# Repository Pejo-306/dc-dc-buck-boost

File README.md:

# DC-DC Buck-Boost Converter - Diploma Project

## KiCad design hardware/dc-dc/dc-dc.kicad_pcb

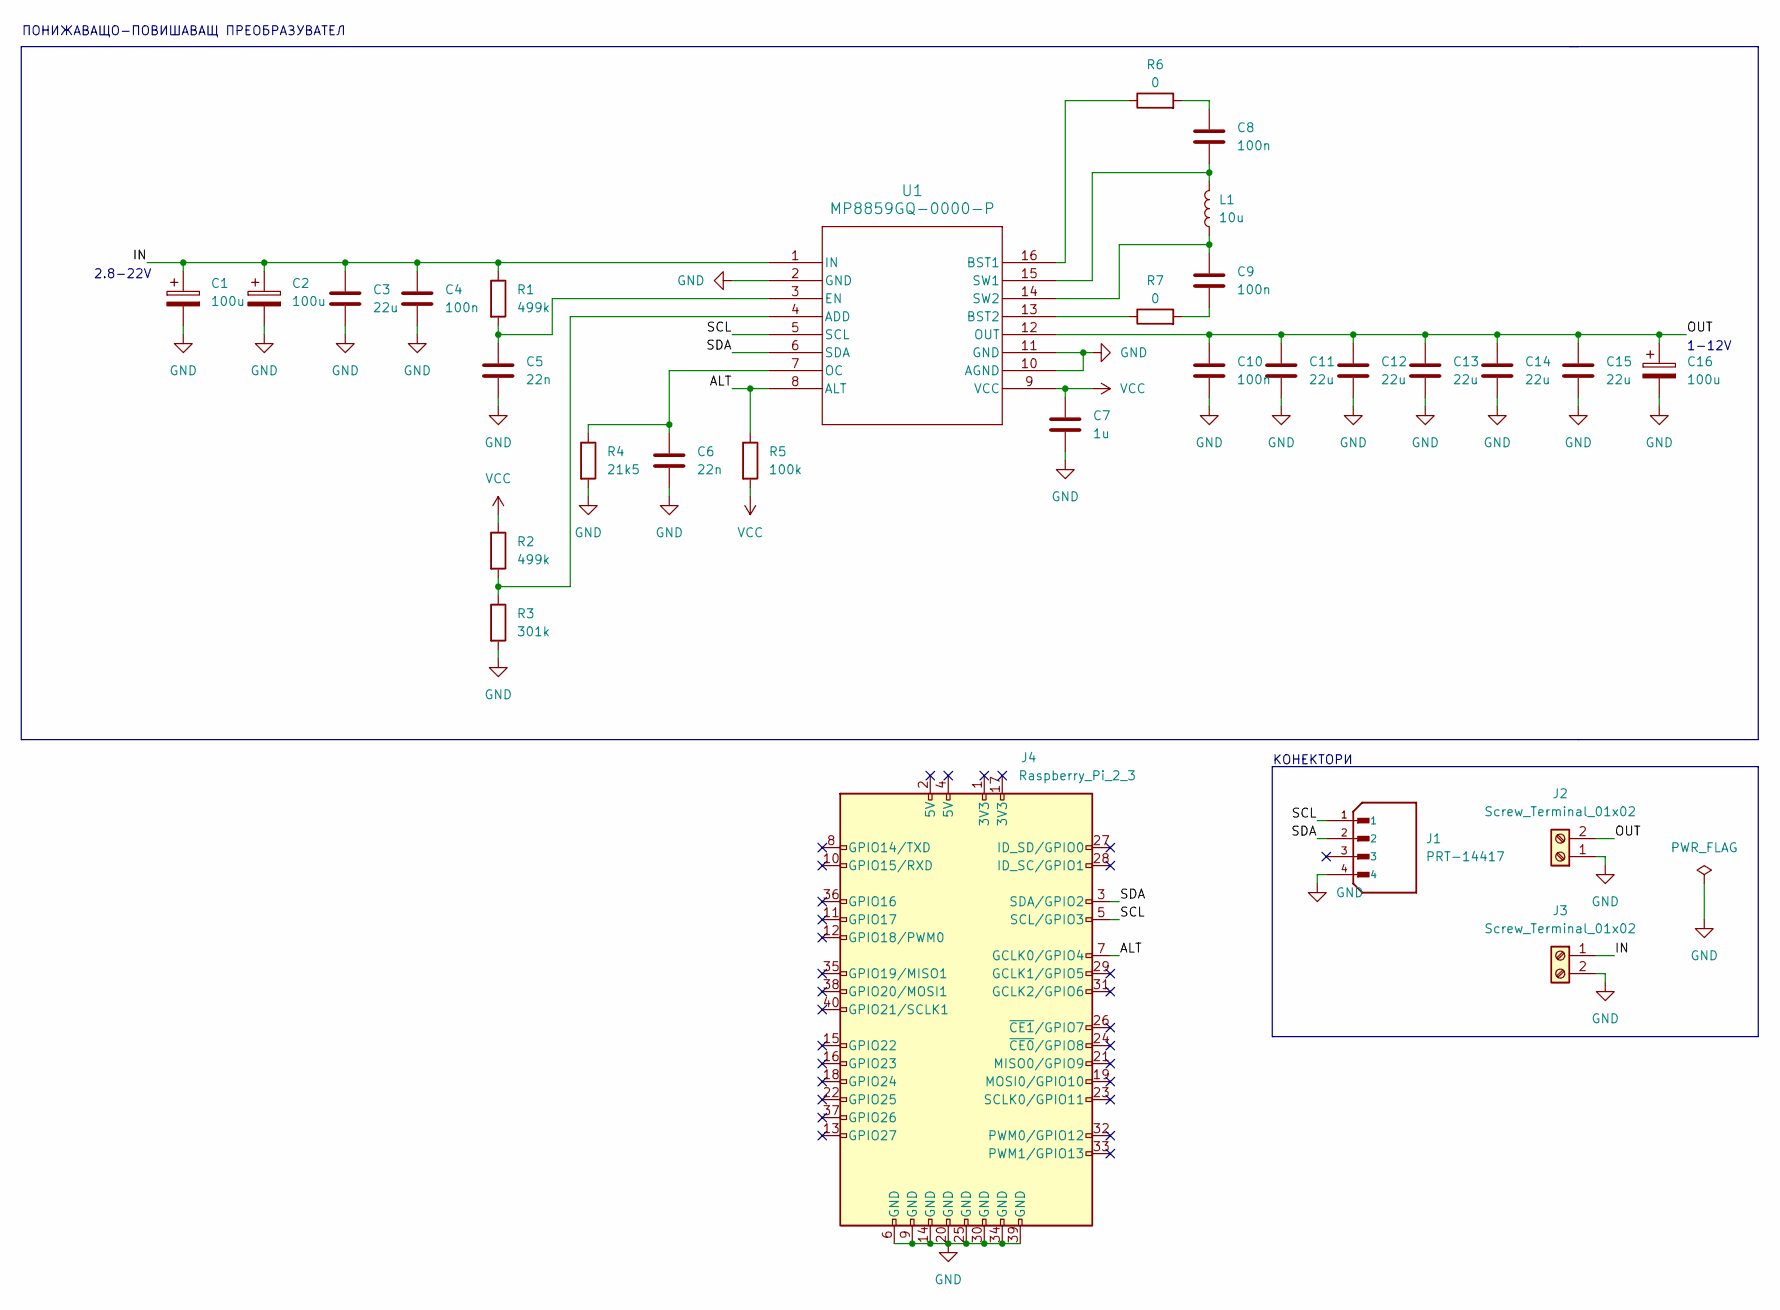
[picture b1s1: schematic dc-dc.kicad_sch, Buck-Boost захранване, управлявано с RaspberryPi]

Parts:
C1, C16: 100u; CP_Elec_6.3x7.7
C2: 100u; CP_EIA-7343-43_Kemet-X_Pad2.25x2.55mm_HandSolder
C3, C11, C12, C13, C14, C15: 22u; C_1206_3216Metric_Pad1.33x1.80mm_HandSolder
C4, C8, C9, C10: 100n; C_0402_1005Metric_Pad0.74x0.62mm_HandSolder
C5, C6: 22n; C_0402_1005Metric_Pad0.74x0.62mm_HandSolder
C7: 1u; C_0603_1608Metric_Pad1.08x0.95mm_HandSolder
J1: PRT-14417; SPARKFUN_PRT-14417; PARTREV NA
J2, J3: Screw_Terminal_01x02; TerminalBlock_Phoenix_PT-1,5-2-3.5-H_1x02_P3.50mm_Horizontal
J4: Raspberry_Pi_2_3
L1: 10u; IND_7050-WE-LHMI_WRE
R1, R2: 499k; R_0402_1005Metric_Pad0.72x0.64mm_HandSolder
R3: 301k; R_0402_1005Metric_Pad0.72x0.64mm_HandSolder
R4: 21k5; R_0402_1005Metric_Pad0.72x0.64mm_HandSolder
R5: 100k; R_0402_1005Metric_Pad0.72x0.64mm_HandSolder
R6, R7: 0; R_0402_1005Metric_Pad0.72x0.64mm_HandSolder
U1: MP8859GQ-0000-P; QFN-16_MP8859_00_MNP

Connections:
/ALT: J4.7 (GCLK0/GPIO4), R5.1, U1.8 (ALT)
/IN: C1.1, C2.1, C3.1, C4.1, J3.1, R1.1, U1.1 (IN)
/OUT: C10.1, C11.1, C12.1, C13.1, C14.1, C15.1, C16.1, J2.2, U1.12 (OUT)
/SCL: J1.1, J4.5 (SCL/GPIO3), U1.5 (SCL)
/SDA: J1.2, J4.3 (SDA/GPIO2), U1.6 (SDA)
GND: C1.2, C2.2, C3.2, C4.2, C5.2, C6.2, C7.2, C10.2, C11.2, C12.2, C13.2, C14.2, C15.2, C16.2, J1.4, J2.1, J3.2, J4.6 (GND), J4.9 (GND), J4.14 (GND), J4.20 (GND), J4.25 (GND), J4.30 (GND), J4.34 (GND), J4.39 (GND), R3.2, R4.2, U1.2 (GND), U1.10 (AGND), U1.11 (GND)
unnamed: C8.2, R6.2
unnamed: C9.1, R7.2
unnamed: R2.2, R3.1, U1.4 (ADD)
unnamed: R6.1, U1.16 (BST1)
unnamed: R7.1, U1.13 (BST2)
unnamed: C5.1, R1.2, U1.3 (EN)
unnamed: C6.1, R4.1, U1.7 (OC)
unnamed: C8.1, L1.2, U1.15 (SW1)
unnamed: C9.2, L1.1, U1.14 (SW2)
VCC: C7.1, R2.1, R5.2, U1.9 (VCC)

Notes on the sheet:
ПОНИЖАВАЩО-ПОВИШАВАЩ ПРЕОБРАЗУВАТЕЛ
КОНЕКТОРИ
1-12V
2.8-22V

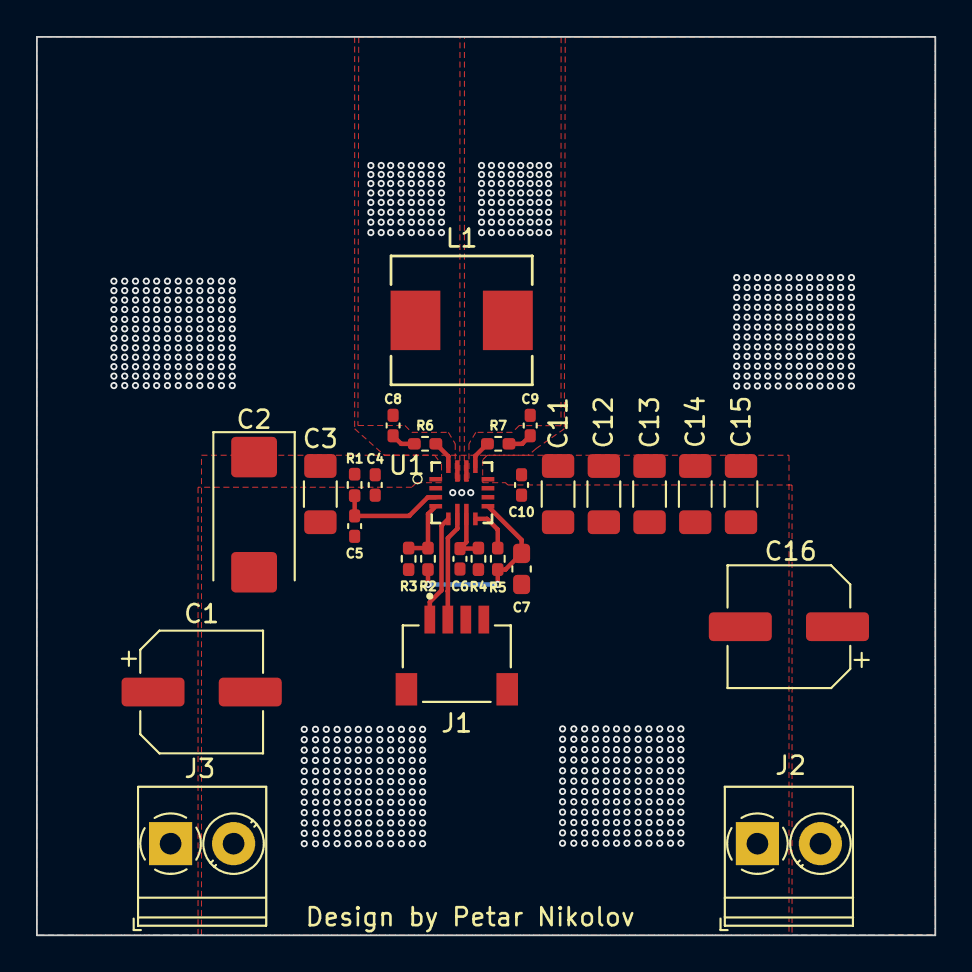
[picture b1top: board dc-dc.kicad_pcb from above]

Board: 4 copper layers, 49.9 x 49.9 mm, 28 parts (0 on the bottom side), 16 nets.

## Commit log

2023-11-13 Create LICENSE
2023-11-13 [SCHEMATIC] Setup KiCad project
2023-12-14 [PCB] Add PCB
2024-01-17 [SIMULATIONS] Add results of power circuit simulations BACKUP
2024-01-17 [SIMULATION] Add schematic for buck-mode power schematic
2024-01-17 [SIMULATION] Add simulation schematic for boost-mode power circuit
2024-01-17 [SIMULATION] Add simulation schematic for buck-boost power circuit
2024-01-17 [PCB] Add minor changes to PCB
2024-01-17 [SIMULATION] Add Smath calculations for buck-boost times
2024-02-04 [Schematic/PCB] Add qwiic connector and 2 electrolytic caps
